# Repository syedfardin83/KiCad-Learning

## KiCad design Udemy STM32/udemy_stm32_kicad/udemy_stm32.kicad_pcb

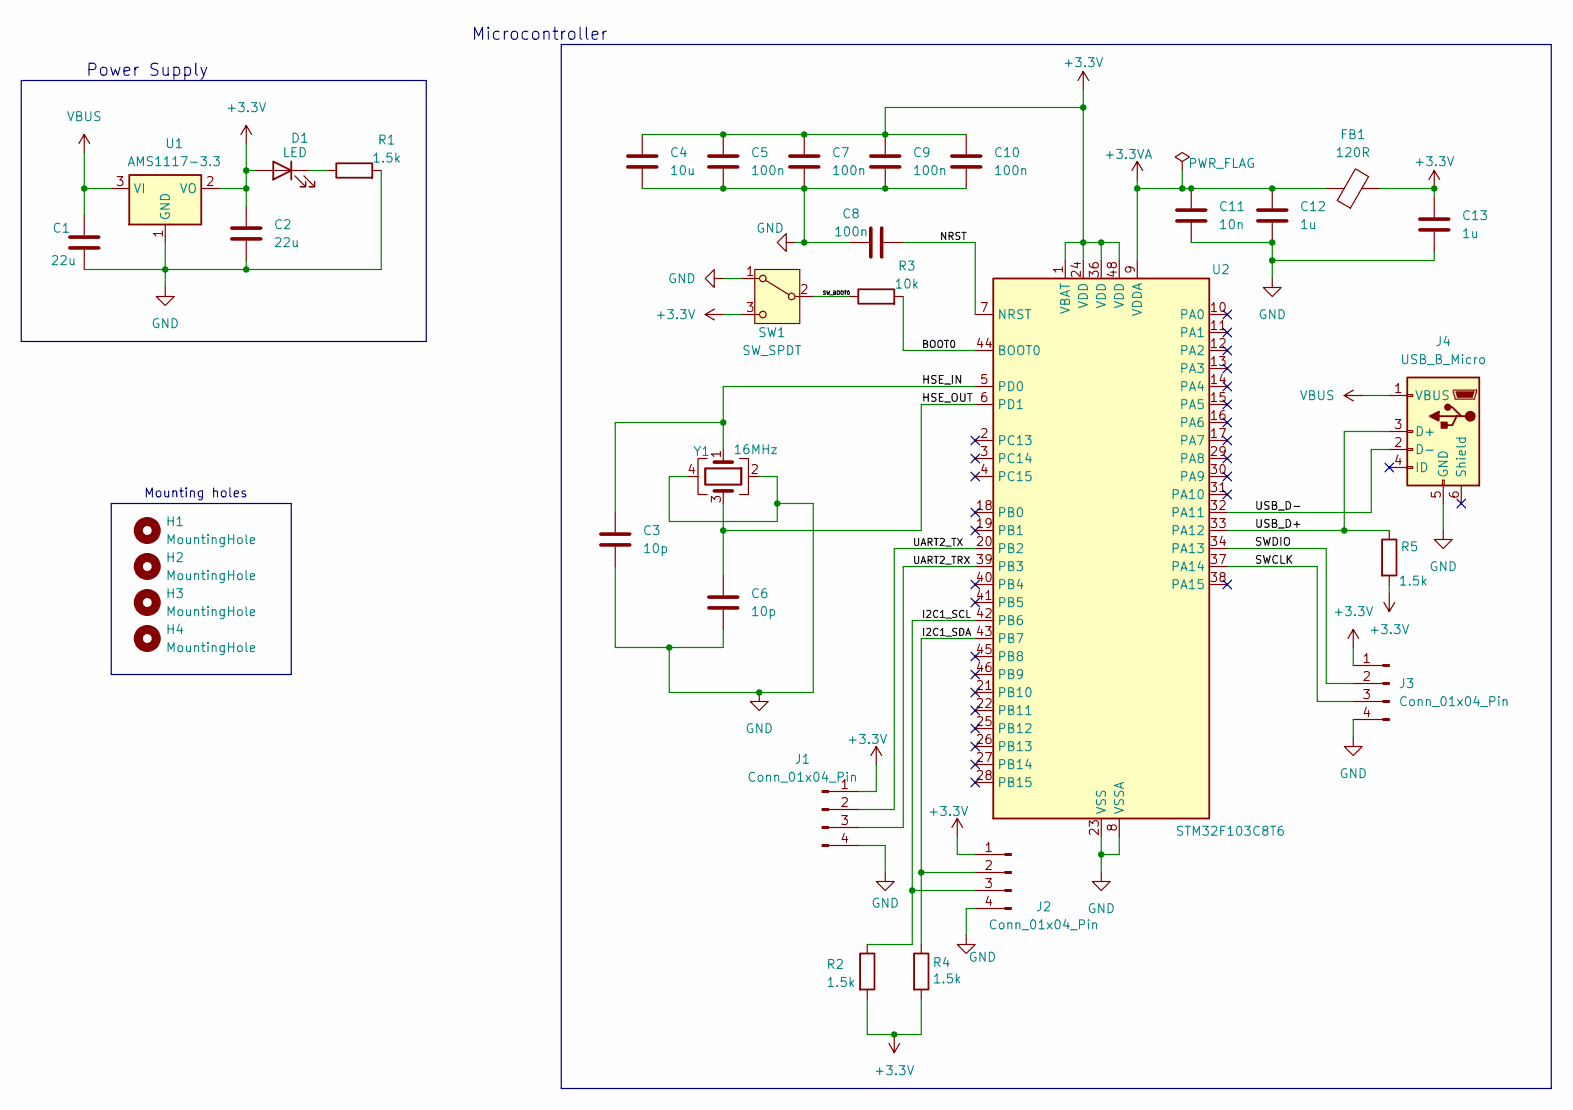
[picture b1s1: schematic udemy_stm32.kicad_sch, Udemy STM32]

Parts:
C1, C2: 22u; C_0805_2012Metric
C3, C6: 10p; C_0402_1005Metric
C4: 10u; C_0603_1608Metric
C5, C7, C8, C9, C10: 100n; C_0402_1005Metric
C11: 10n; C_0402_1005Metric
C12, C13: 1u; C_0402_1005Metric
D1: LED; LED_0603_1608Metric
FB1: 120R; L_0603_1608Metric
H1, H2, H3, H4: MountingHole; MountingHole_2.2mm_M2
J1, J2, J3: Conn_01x04_Pin; PinHeader_1x04_P2.54mm_Vertical
J4: USB_B_Micro; USB_Micro-B_Wuerth_629105150521
R1, R2, R4, R5: 1.5k; R_0402_1005Metric
R3: 10k; R_0402_1005Metric
SW1: SW_SPDT; SW_SPDT_PCM12
U1: AMS1117-3.3; SOT-223-3_TabPin2
U2: STM32F103C8T6; LQFP-48_7x7mm_P0.5mm
Y1: 16MHz; Crystal_SMD_3225-4Pin_3.2x2.5mm

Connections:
+3.3V: C2.1, C4.1, C5.1, C7.1, C9.1, C10.1, C13.1, D1.2 (A), FB1.2, J1.1, J2.1, J3.1, R2.2, R4.2, R5.2, SW1.3 (C), U1.2 (VO), U2.1 (VBAT), U2.24 (VDD), U2.36 (VDD), U2.48 (VDD)
+3.3VA: C11.1, C12.1, FB1.1, U2.9 (VDDA)
/BOOT0: R3.2, U2.44 (BOOT0)
/HSE_IN: C3.1, U2.5 (PD0), Y1.1
/HSE_OUT: C6.1, U2.6 (PD1), Y1.3
/I2C1_SCL: J2.3, R2.1, U2.42 (PB6)
/I2C1_SDA: J2.2, R4.1, U2.43 (PB7)
/NRST: C8.2, U2.7 (NRST)
/SWCLK: J3.3, U2.37 (PA14)
/SWDIO: J3.2, U2.34 (PA13)
/SW_BOOT0: R3.1, SW1.2 (B)
/UART2_TRX: J1.3, U2.39 (PB3)
/UART2_TX: J1.2, U2.20 (PB2)
/USB_D+: J4.3 (D+), R5.1, U2.33 (PA12)
/USB_D-: J4.2 (D-), U2.32 (PA11)
GND: C1.2, C2.2, C3.2, C4.2, C5.2, C6.2, C7.2, C8.1, C9.2, C10.2, C11.2, C12.2, C13.2, J1.4, J2.4, J3.4, J4.5 (GND), R1.2, SW1.1 (A), U1.1 (GND), U2.8 (VSSA), U2.23 (VSS), U2.35 (VSS), U2.47 (VSS), Y1.2, Y1.4
unnamed: D1.1 (K), R1.1
VBUS: C1.1, J4.1 (VBUS), U1.3 (VI)

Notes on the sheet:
Mounting holes
Microcontroller
Power Supply

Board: 2 copper layers, 32 parts (0 on the bottom side), 18 nets, no tracks yet.

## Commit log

2025-07-05 Powering done, bootloader circuit done
2025-07-06 Crystal added
2025-07-07 Schematic and footprint completed
2025-07-08 backup
2025-07-11 PCB rough design half done
2025-07-11 PCB rough design done
2025-07-13 Tinkering around for good placements
